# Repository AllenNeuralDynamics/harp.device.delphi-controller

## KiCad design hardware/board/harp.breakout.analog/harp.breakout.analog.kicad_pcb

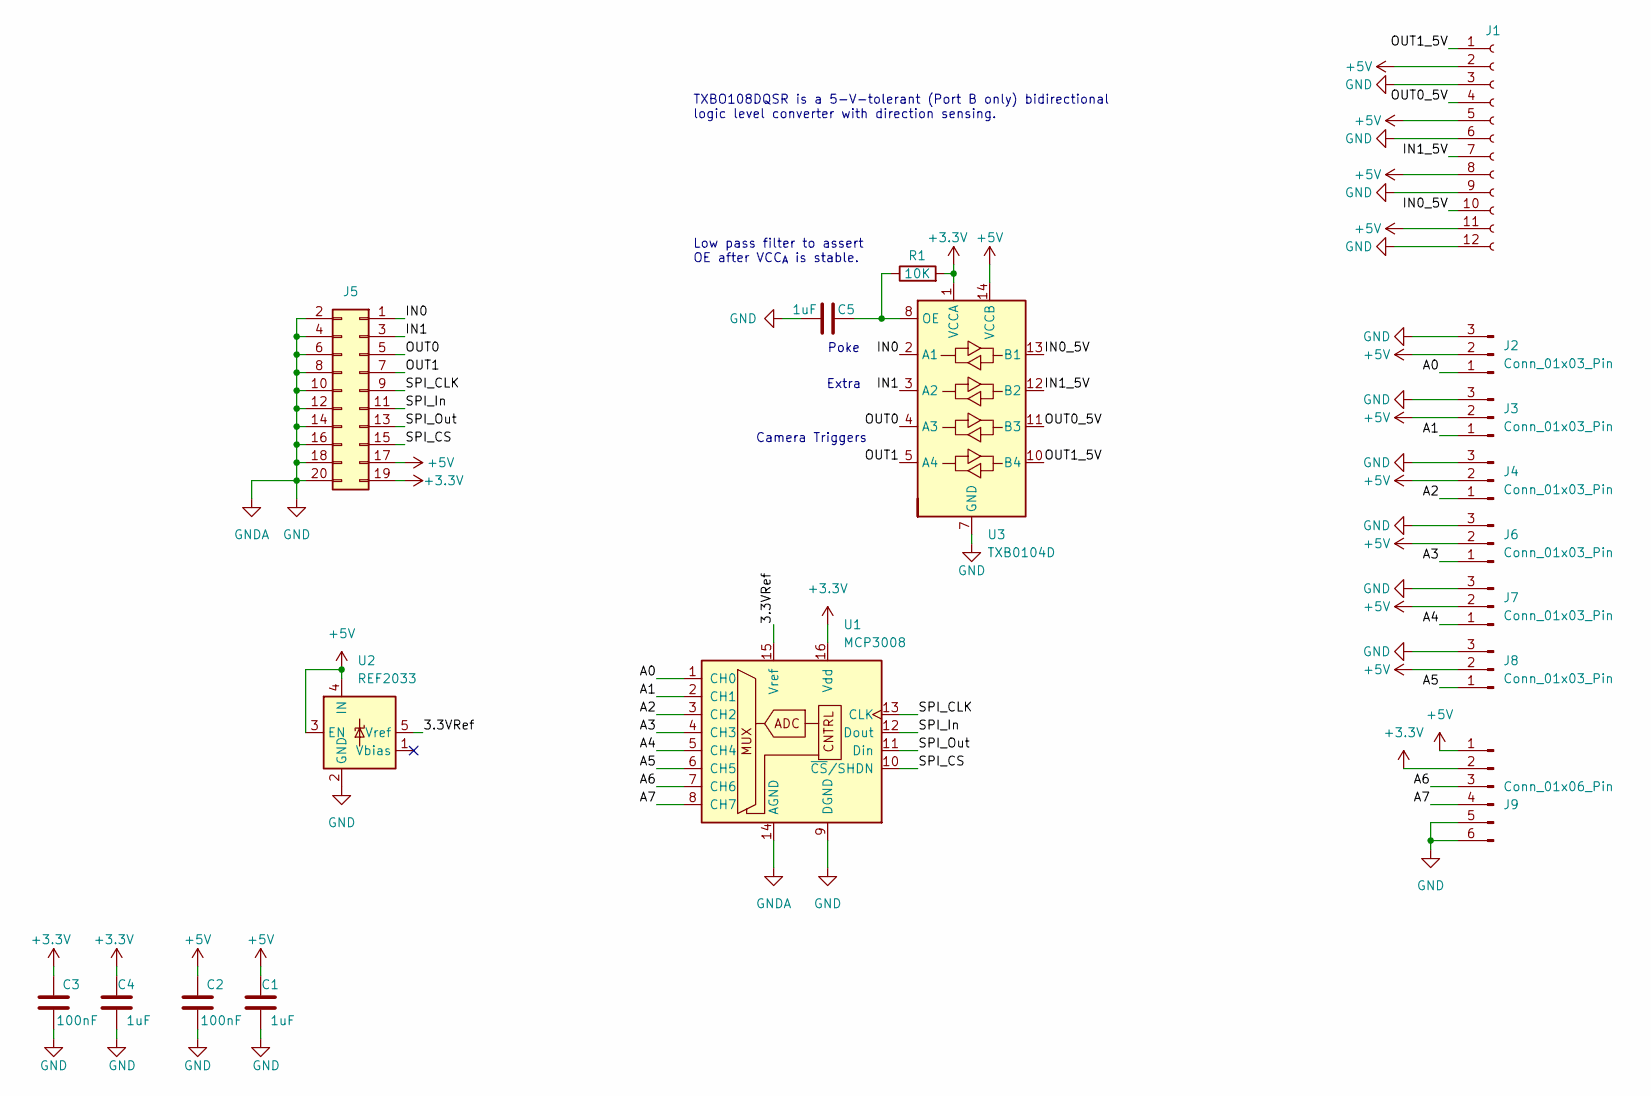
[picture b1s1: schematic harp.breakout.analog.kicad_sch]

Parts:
C1, C4, C5: 1uF; C_0402_1005Metric_Pad0.74x0.62mm_HandSolder; Rated Voltage 35V
C2, C3: 100nF; C_0402_1005Metric_Pad0.74x0.62mm_HandSolder; Rated Voltage 50V; Tolerance 10%
J1: Conn_01x12_Socket; 3M_Mini-Clamp-Socket-37212-62M3-003PL-3x4_Vertical
J2, J3, J4, J6, J7, J8: Conn_01x03_Pin; CONN_705530002_03_MOL
J5: Conn_02x10_Odd_Even; PinSocket_2x10_P2.54mm_Vertical
J9: Conn_01x06_Pin; PinHeader_1x06_P2.54mm_Vertical
R1: 10K; R_0402_1005Metric_Pad0.72x0.64mm_HandSolder
U1: MCP3008; DIP-16_W7.62mm_LongPads
U2: REF2033; SOT-23-5
U3: TXB0104D; SOIC-14_3.9x8.7mm_P1.27mm

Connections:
+3.3V: C3.2, C4.1, J5.19, J9.2, R1.2, U1.16 (Vdd), U3.1 (VCCA); also elsewhere on the board
+5V: C1.1, C2.2, J1.2, J1.5, J1.8, J1.11, J2.2, J3.2, J4.2, J5.17, J6.2, J7.2, J8.2, J9.1, U2.3 (EN), U2.4 (IN), U3.14 (VCCB); also elsewhere on the board
/3.3VRef: U1.15 (Vref), U2.5 (Vref); also elsewhere on the board
/A0: J2.1, U1.1 (CH0)
/A1: J3.1, U1.2 (CH1)
/A2: J4.1, U1.3 (CH2)
/A3: J6.1, U1.4 (CH3)
/A4: J7.1, U1.5 (CH4)
/A5: J8.1, U1.6 (CH5)
/A6: J9.3, U1.7 (CH6)
/A7: J9.4, U1.8 (CH7)
/IN0: J5.1, U3.2 (A1)
/IN0_5V: J1.10, U3.13 (B1)
/IN1: J5.3, U3.3 (A2)
/IN1_5V: J1.7, U3.12 (B2)
/OUT0: J5.5, U3.4 (A3)
/OUT0_5V: J1.4, U3.11 (B3)
/OUT1: J5.7, U3.5 (A4)
/OUT1_5V: J1.1, U3.10 (B4)
/SPI_CLK: J5.9, U1.13 (CLK)
/SPI_CS: J5.15, U1.10 (~CS/SHDN)
/SPI_In: J5.11, U1.12 (Dout)
/SPI_Out: J5.13, U1.11 (Din)
GND: C1.2, C2.1, C3.1, C4.2, C5.2, J1.3, J1.6, J1.9, J1.12, J2.3, J3.3, J4.3, J5.2, J5.4, J5.6, J5.8, J5.10, J5.12, J5.14, J5.16, J5.18, J5.20, J6.3, J7.3, J8.3, J9.5, J9.6, U1.9 (DGND), U1.14 (AGND), U2.2 (GND), U3.7 (GND); also elsewhere on the board
unnamed: C5.1, R1.1, U3.8 (OE)

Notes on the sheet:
Camera Triggers
Low pass filter to assert OE after VCC_{A} is stable.
Poke
TXBO108DQSR is a 5-V-tolerant (Port B only) bidirectional logic level converter with direction sensing.
Extra

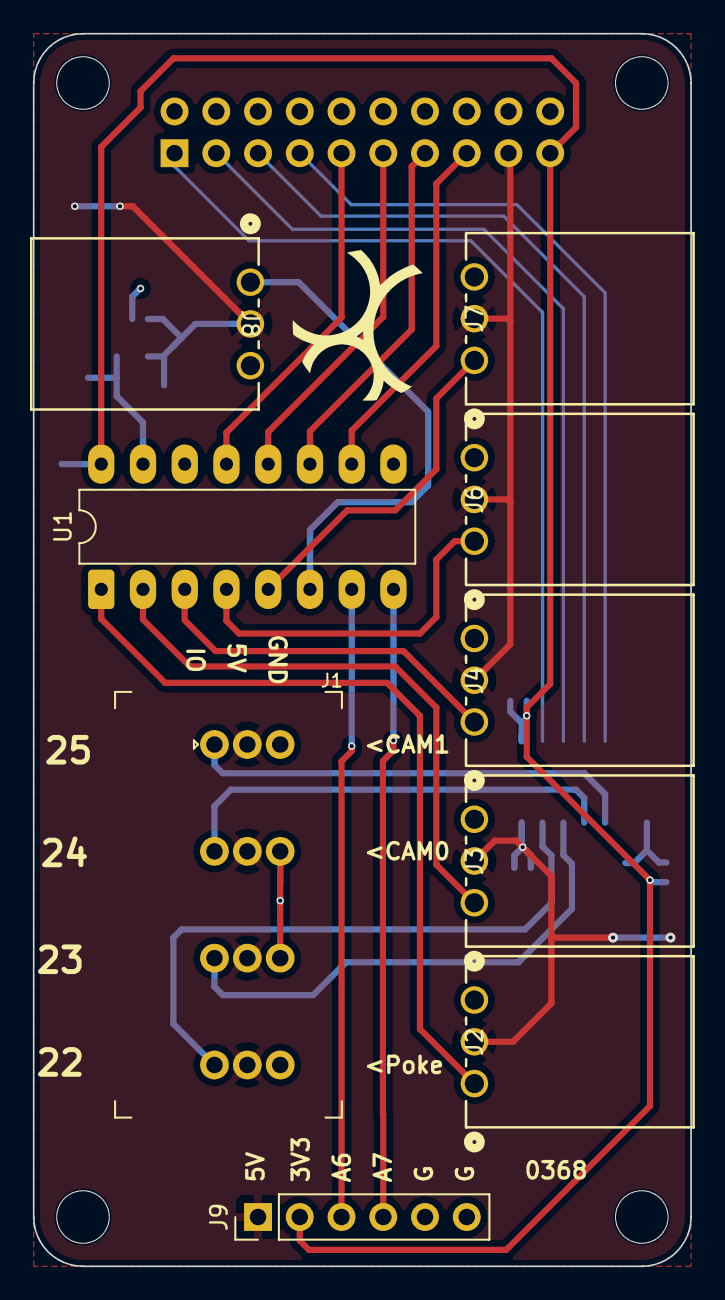
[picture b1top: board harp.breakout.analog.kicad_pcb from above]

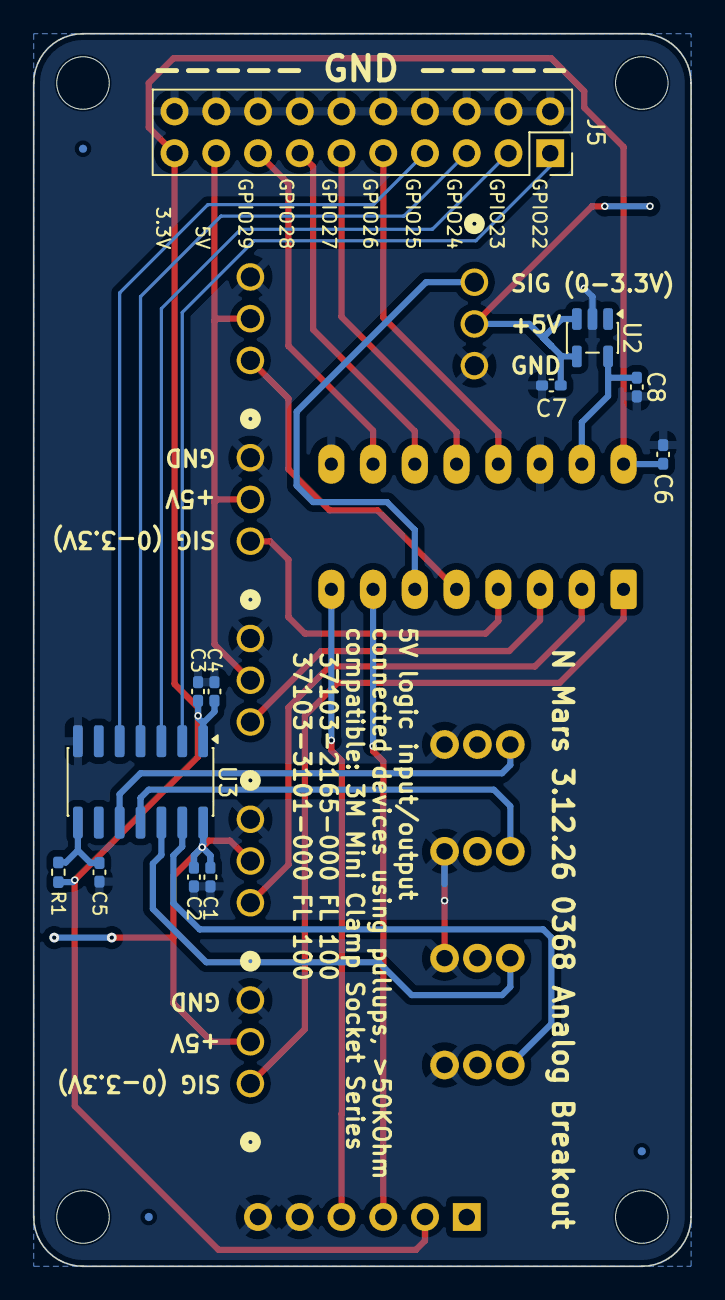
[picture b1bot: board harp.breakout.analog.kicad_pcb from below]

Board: 2 copper layers, 40.0 x 75.0 mm, 24 parts (15 on the bottom side), 25 nets.

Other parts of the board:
C6: 1uF; C_0402_1005Metric_Pad0.74x0.62mm_HandSolder
C7, C8: 0.1uF; C_0402_1005Metric_Pad0.74x0.62mm_HandSolder
FID2, FID2#2, FID2#3: Fiducial; Fiducial_0.5mm_Mask1mm

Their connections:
+3.3V: C6.1; also elsewhere on the board
+5V: C7.1; also elsewhere on the board
/3.3VRef: C8.1; also elsewhere on the board
GND: C6.2, C7.2, C8.2; also elsewhere on the board

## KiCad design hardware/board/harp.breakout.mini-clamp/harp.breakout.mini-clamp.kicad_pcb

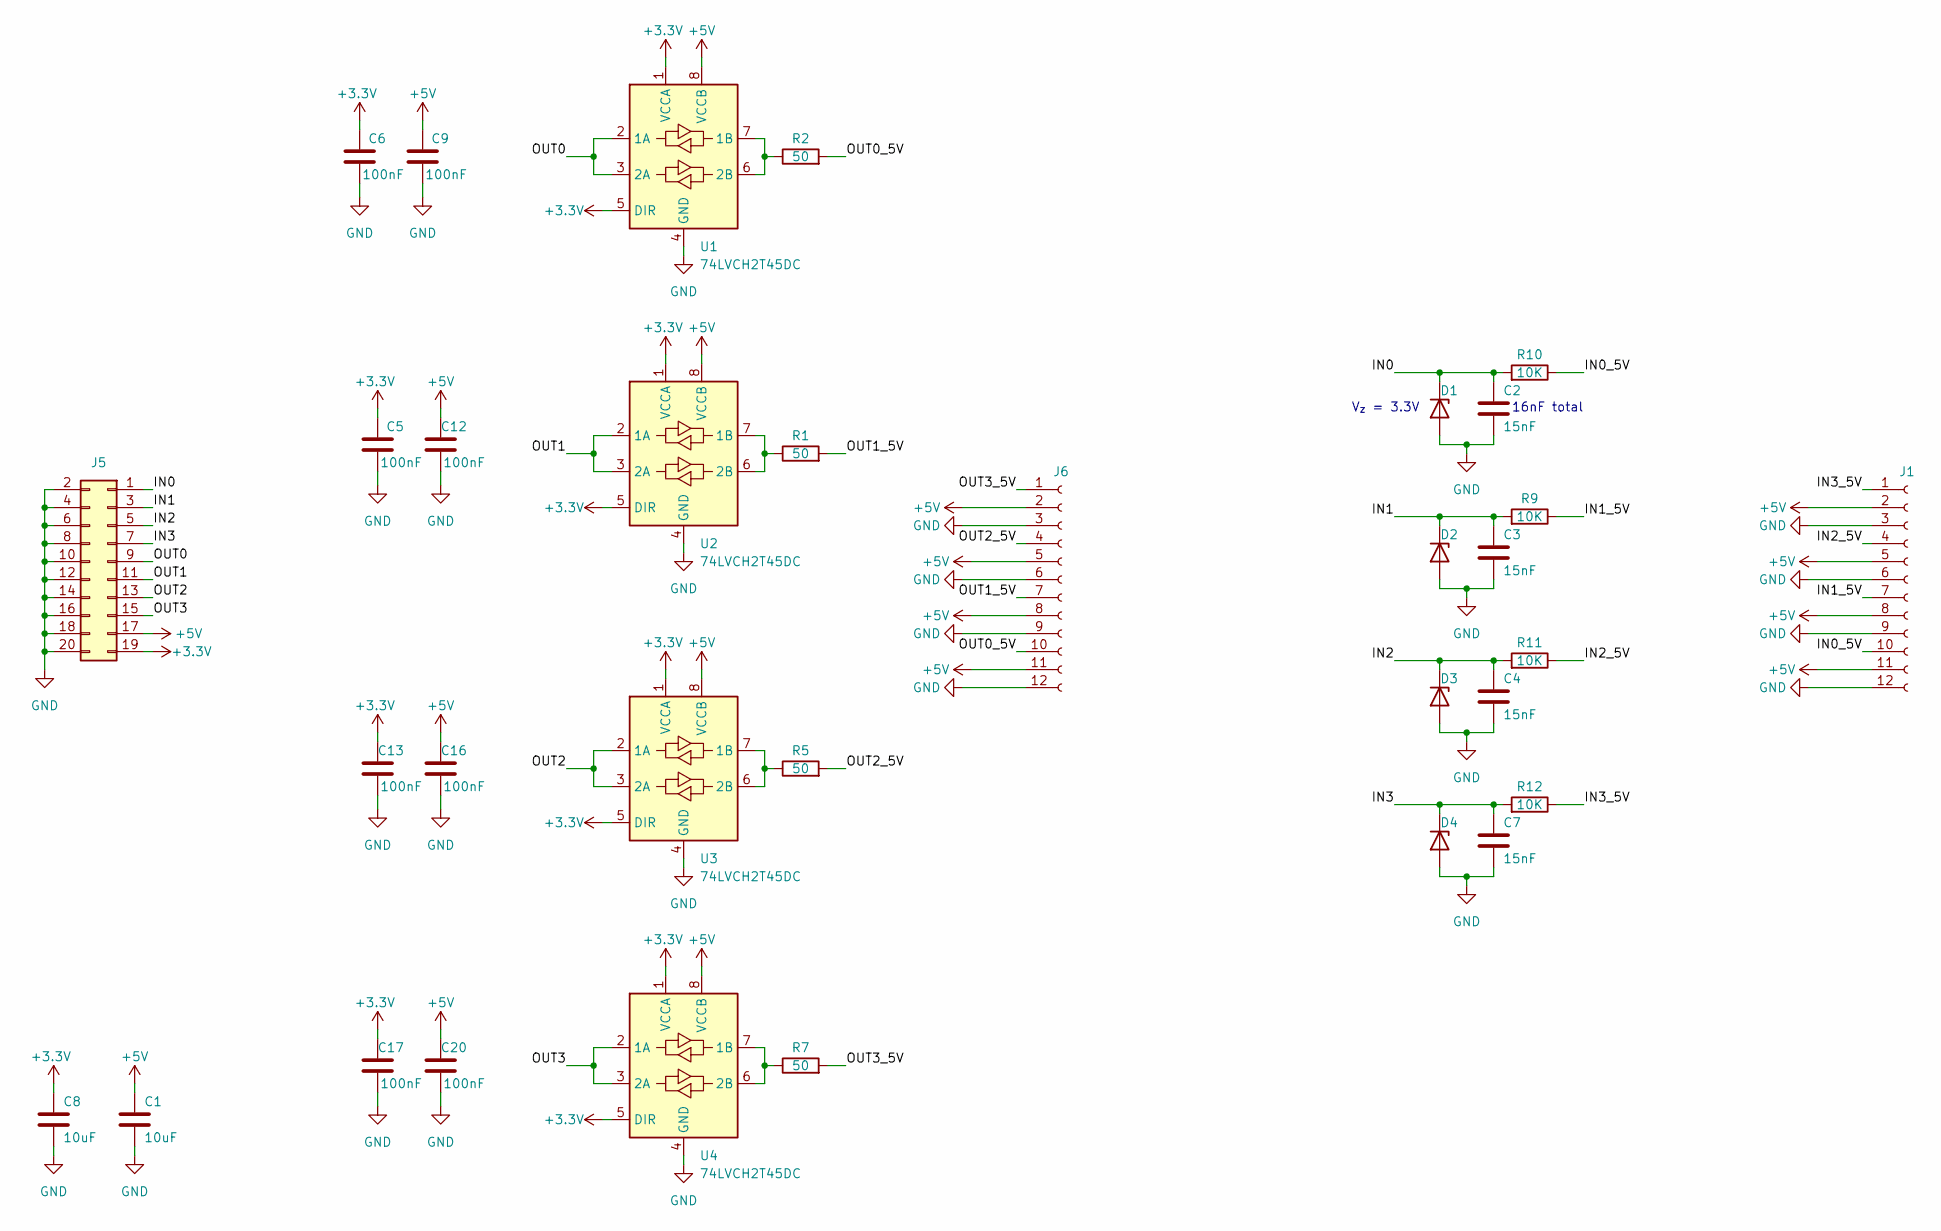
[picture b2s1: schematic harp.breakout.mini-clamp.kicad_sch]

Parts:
C1, C8: 10uF; C_0805_2012Metric; Rated Voltage 25V
C2, C3, C4, C7: 15nF; C_0402_1005Metric
C5, C6, C9, C12, C13, C16, C17, C20: 100nF; C_0402_1005Metric; Rated Voltage 16V; Tolerance 10%
D1, D2, D3, D4: D_Zener; D_SOD-323
J1, J6: Conn_01x12_Socket; 3M_Mini-Clamp-Socket-37212-62M3-003PL-3x4_Vertical
J5: Conn_02x10_Odd_Even; PinSocket_2x10_P2.54mm_Vertical
R1, R2, R5, R7: 50; R_1206_3216Metric; Tolerance 1%
R9, R10, R11, R12: 10K; R_0402_1005Metric
U1, U2, U3, U4: 74LVCH2T45DC; VSSOP-8_2.3x2mm_P0.5mm

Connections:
+3.3V: C5.2, C6.2, C8.1, C13.2, C17.2, J5.19, U1.1 (VCCA), U1.5 (DIR), U2.1 (VCCA), U2.5 (DIR), U3.1 (VCCA), U3.5 (DIR), U4.1 (VCCA), U4.5 (DIR)
+5V: C1.1, C9.2, C12.2, C16.2, C20.2, J1.2, J1.5, J1.8, J1.11, J5.17, J6.2, J6.5, J6.8, J6.11, U1.8 (VCCB), U2.8 (VCCB), U3.8 (VCCB), U4.8 (VCCB)
/IN0: C2.1, D1.1 (K), J5.1, R10.2
/IN0_5V: J1.10, R10.1
/IN1: C3.1, D2.1 (K), J5.3, R9.2
/IN1_5V: J1.7, R9.1
/IN2: C4.1, D3.1 (K), J5.5, R11.2
/IN2_5V: J1.4, R11.1
/IN3: C7.1, D4.1 (K), J5.7, R12.2
/IN3_5V: J1.1, R12.1
/OUT0: J5.9, U1.2 (1A), U1.3 (2A)
/OUT0_5V: J6.10, R2.2
/OUT1: J5.11, U2.2 (1A), U2.3 (2A)
/OUT1_5V: J6.7, R1.2
/OUT2: J5.13, U3.2 (1A), U3.3 (2A)
/OUT2_5V: J6.4, R5.2
/OUT3: J5.15, U4.2 (1A), U4.3 (2A)
/OUT3_5V: J6.1, R7.2
GND: C1.2, C2.2, C3.2, C4.2, C5.1, C6.1, C7.2, C8.2, C9.1, C12.1, C13.1, C16.1, C17.1, C20.1, D1.2 (A), D2.2 (A), D3.2 (A), D4.2 (A), J1.3, J1.6, J1.9, J1.12, J5.2, J5.4, J5.6, J5.8, J5.10, J5.12, J5.14, J5.16, J5.18, J5.20, J6.3, J6.6, J6.9, J6.12, U1.4 (GND), U2.4 (GND), U3.4 (GND), U4.4 (GND)
unnamed: R2.1, U1.6 (2B), U1.7 (1B)
unnamed: R1.1, U2.6 (2B), U2.7 (1B)
unnamed: R5.1, U3.6 (2B), U3.7 (1B)
unnamed: R7.1, U4.6 (2B), U4.7 (1B)

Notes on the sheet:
16nF total
V_{z} = 3.3V

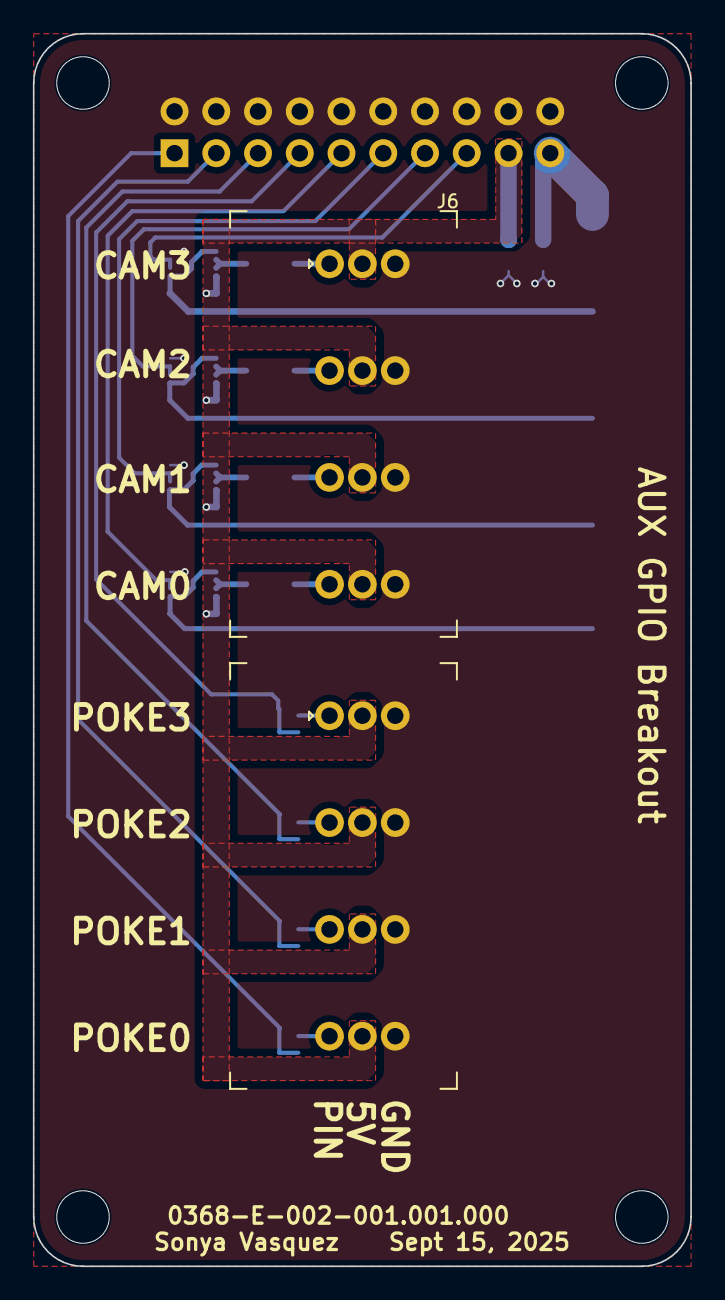
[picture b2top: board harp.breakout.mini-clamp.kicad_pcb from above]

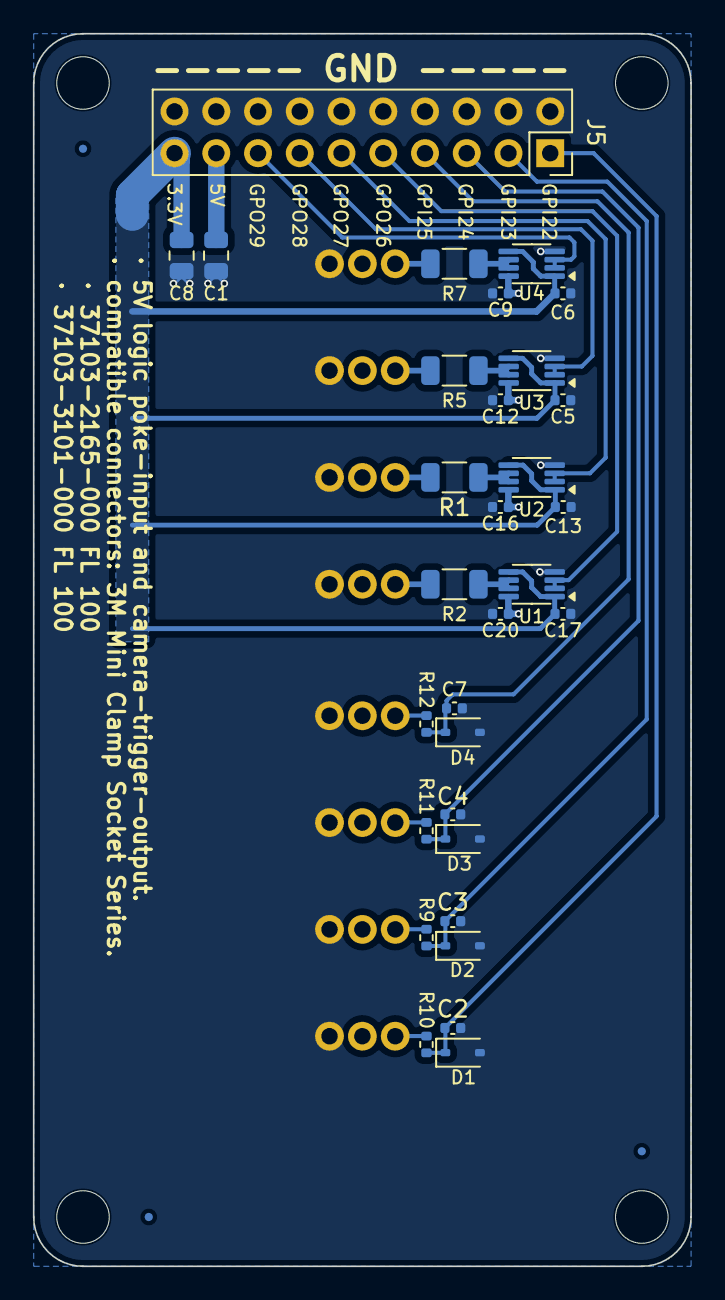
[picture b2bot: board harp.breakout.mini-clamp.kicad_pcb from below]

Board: 2 copper layers, 40.0 x 75.0 mm, 36 parts (34 on the bottom side), 23 nets.

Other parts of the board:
FID2, FID2#2, FID2#3: Fiducial; Fiducial_0.5mm_Mask1mm

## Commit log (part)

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2025-04-09 draft poke manager
2025-04-10 Draft poke manager tests
2025-04-16 Poke manager test bed
2025-04-28 FSM logic for delphi controller
2025-04-29 Detect pokes and update FSM
2025-04-30 Updated transition duration values
2025-05-02 Added poke manager test files and started to add registers and harp protocol functionality
2025-05-05 Added poke detection functionality into poke manager
2025-05-29 Started implementing harp registers and protocol functionality
2025-06-09 get project compiling; fix harp write fns
2025-06-09 draft device.yml
2025-06-09 inline short setters; fix pass sub-array-by-reference
2025-06-10 split writing config into separate registers
2025-06-11 update pyharp registers
2025-06-11 cleanup reset state
2025-06-11 add request-next-odor callback
2025-08-08 update poke-manager test; get gpio inversion working
2025-08-08 get next-odor event request working
2025-08-08 add wait for pokes script
2025-09-12 fixed setting some state duration registers
2025-09-15 made remaining valves odor valves
2025-09-15 fixed odor queue functionality and poke state
2025-09-15 update mini clamp board
2025-09-17 fixed poke state register and added events for pokes
2025-09-17 added min and max odor delivery time functionality
2025-09-17 added raw poke state register and rise and fall events
2025-09-19 added camera driver firmware
2025-09-22 fixed camera triggering
2025-09-23 added pwm events and updated register documentation
2025-09-26 added register for enabling or disabling valve LEDs
2025-10-06 Initial interface project setup from reflex-generator
2025-10-06 Build interface from top level device.yml
2025-10-06 Build interface for additional registers
2025-10-10 Fixed event-based odor indexing and minor documentation errors
2025-10-29 Pokes are only registered during the pre-odor delivery state
2025-10-29 Fixed raw poke state read register
2025-11-19 Fixed GPIO masking
2025-11-20 Updated GPIO indices in device.yaml
2025-11-20 Refactorization for queuing an arbitrary number of odors
2025-11-25 update breakout
2025-11-26 Event for valve state changes
2025-12-01 Update register descriptions and access
2025-12-09 Fix device id
2025-12-23 Poke detection only during odor exhaust state
2026-01-31 Refactor valve controller state machine
2026-02-04 Clean up code
2026-02-06 GPIO reconfiguration
2026-02-13 Configure and read from ADCs
2026-02-13 Alerts for detected leaks
2026-02-13 Force fsm test
2026-02-13 Flow rate alerts for manual flow meter
2026-02-16 Flow rate calibration registers and conversions
2026-02-17 Multiple pio pwm outputs
2026-02-17 Fix multiple pwm outputs
2026-02-26 Write to valveconfig register to test proportional valve
2026-02-28 Proportional valve PID controller
2026-03-11 Initial schematic
2026-03-12 Analog Breakout layout
2026-03-18 Code clean up
2026-03-18 Odor dwell time register and automatic odor update with rule changes
2026-03-23 Configurable odor dwell time and fix poke pin initialization
2026-03-23 Test code from bench test
2026-04-01 ADC spi configuration for measuring flow rate
2026-04-01 ADC reconfiguration and reads for raw ADC samples
2026-04-02 Removed unused ADC sample rate register
2026-04-03 Flow meter calibration struct for individual calibrations
2026-04-03 Vacuum flow control
2026-04-03 MCP3208 SPI 12bit updates
2026-04-09 Minor analog board silk updates
2026-04-11 Added bypass caps and updated BOM
2026-04-11 Rebuild GND plane
2026-04-11 Attempting a test GUI
2026-04-13 Added valves, ADC, PID to GUI (untested)
2026-04-13 Fixed firmware bugs and updated documentation and testing script
2026-04-14 Working on valves
2026-04-14 Nonlinear flow meter estimate
2026-04-15 Improved silkscreen and corrected SPI pins
2026-04-15 Dwell time addition to test script
2026-04-16 Created pid_timing.py to time odor delivery, notes in pid_timing_notes.md
2026-04-16 Removed excess data files
2026-04-16 Minor updates to pid_timing.py
2026-04-17 Added pid_timing_no_pokes.py
2026-04-17 primed odor test
2026-05-08 Add second output pio pwm for camera triggering
2026-05-11 sipe_bench_testing init commit
2026-05-12 fix flowtest scripts
2026-05-29 Improved test notes
2026-05-29 Add purge step
2026-06-02 sequential tests
2026-06-03 Added a register to prevent PID updates when final valve is open
